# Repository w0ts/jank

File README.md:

# Jank

> ## [→ w0ts.github.io/jank](https://w0ts.github.io/jank/)
> **What Jank is, how to install it from the browser, and the device's control page: on the site.**
> This README is for developers.

Jank brings computers, MIDI gear and modular gear into one Ableton Link session with no router: the group mode of
[Optimist](https://github.com/w0ts/optimist), the open firmware for the FM-1 synth. Link is Ableton's trademark; Jank is
not an Ableton product.

## Build and flash

```
scripts/install_idf.sh       # once: ESP-IDF v5.5.6 into the scratch folder (needs Python 3.13)
make build                   # scripts/build.sh auto: the release image, XIAO or jank mini 3, told apart at the start
make flash                   # build, then install on the running device: the JANK drive, else USB MIDI (scripts/ota.py)
bash tests/run.sh            # the host tests (C and the pages' JS)
```

Build files stay in `$JANK_SCRATCH` (default `worktrees/jank-scratch/`, git-ignored). Boards, builds, partitions and
updates: [docs/firmware.md](docs/firmware.md), [docs/boards.md](docs/boards.md), [docs/usb.md](docs/usb.md).

## Site and releases

- `make page` expands `page/src/*.html` (+ `ui/`) into `page/`. The site is built from `main` by the Pages workflow
  (`.github/workflows/pages.yml`, the shared w0ts site builder with `site.json`) whenever `page/` changes; `make publish-page` runs it by hand.
  No branch holds the site.
- A `v*` tag runs `.github/workflows/release.yml`: it builds the release image, `scripts/publish_firmware.py` writes its
  assets (every flash part and the manifest `jank-auto-TAG.json`), the release carries them, and the Pages workflow lays
  them out under the site's `firmware/` (with `firmware/index.json`) for the Install page's browser flasher.

## Hardware

- [jank mini 3](hardware/jank-mini-3/README.md): our board around the Waveshare ESP32-S3-LCD-2, and its printed case
  (`hardware/jank-mini-3/case/`). The bare device is a Seeed XIAO ESP32-S3 alone.

## Docs

[On the air](docs/air.md) · [USB](docs/usb.md) · [MIDI clock](docs/midi.md) · [boards and pins](docs/boards.md) ·
[LCD-2](docs/lcd2.md) · [LINE IN](docs/linein.md) · [beat follow](docs/beat.md)

**Beat follow's network weights are not in the firmware or in this repository.** The firmware reads them from its
`beatw` partition; the Install page adds madmom's model (CC BY-NC-SA 4.0, non-commercial) at the user's click, from
madmom's own repository, in the user's browser ([docs/beat.md](docs/beat.md)).

## Licensing

The firmware (`firmware/`, `core/`, `tests/`, `scripts/`) is GPL-3.0-only, as it links Optimist's `link.c`
(`third_party/link`, copied from fm1-base, see its README). The control page and its test are MIT. The hardware
scripts carry GPL-3.0-only SPDX tags (`hardware/pcb/lib/stitch.py` CC0-1.0); the KiCad footprint of the XIAO is Seeed's,
CC BY-SA 4.0. See [LICENSE](LICENSE).

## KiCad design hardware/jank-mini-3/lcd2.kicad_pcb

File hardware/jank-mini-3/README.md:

# jank-mini-3: the LCD-2 module board (FINAL 2026-11-19: review rounds 9 and 10 clean; not ordered)

A removable add-on board for a Waveshare ESP32-S3-LCD-2 (sku 30306). The LCD-2 sits in our notch, its PCB level with
ours; two bridge strips (strip/), each with two 1 x 14 sockets, plug onto its pins and onto our J15 / J16 (standard
male headers): nothing is soldered between them, a printed support in the case holds the strips from below. No screws.
The plan, cost, sketches and bench tests are in `worktrees/lcd2-addon-scratch/` (README.md there). **The current
order remarks and bench steps are in "Ordering" near the end; the review-round sections are history.**

| file | what |
|---|---|
| `parts.py` | the one parts table: every part, value, LCSC code, pad -> net, the GPIO map, the LCD-2's rows |
| `make_schematic.py` | writes `lcd2.kicad_sch`, `lib/chip.kicad_sym`, `fab/intended-nets.json` (mini 2.2's generator) |
| `check_nets.py` | the KiCad netlist against parts.py, plus the pin rules (LCD-2 rows, ADC1, glitch / pull rules, pull-downs, boost < clamp) |
| `sim/` | `power.py`, `clamp.py`, `host.py`, `midi_cv.py`, `linein_esd.py` and their `.txt` results |
| `lcd2-schematic.pdf` | the sheet (one label per pin: it reads as a netlist) |

Rebuild and check (KiCad 10, ngspice 47, Python with numpy):

```bash
cd hardware/jank-mini-3 && python3 make_schematic.py && kicad-cli sch erc --severity-all -o fab/erc.rpt lcd2.kicad_sch && kicad-cli sch export netlist --format kicadxml -o fab/lcd2.net.xml lcd2.kicad_sch && python3 check_nets.py fab/lcd2.net.xml fab/intended-nets.json
```

```bash
cd hardware/jank-mini-3/sim && for s in power clamp host midi_cv linein_esd; do python3 $s.py > /dev/null || echo FAIL $s; done
```

USB (mots, 2026-11-17): the LCD-2's own USB-C sits at the case's side wall and is used directly for a computer or a
charger. For host mode a standard short cable outside the box joins it to J1 (TO ESP, USB-C, VBUS and CC open); D+ / D-
run straight to J4 (TO DEVICE, USB-C), whose VBUS carries only the host signal (R93 / D16 from U21).

OUT gives hosted gear only a 680 ohm host signal on VBUS, never power (mots, 2026-11-17: the small cell is not drained). Bus-powered gear needs its own power or a powered hub.

## jank-mini-3 layout (mots, 2026-11-18)

Board 95.5 x 82 mm (93 x 74 until round 3: +2.5 mm wide for the mid-mount USB-C pair, +4 mm above and below the
LCD-2 for the bands beside it, mots 2026-11-18), the LCD-2 in a notch open to the left edge (its PCB level with ours,
LCD-2 centred). Two bridge strips (strip/, 37.06 x 10 mm: two 1 x 14 sockets C2905420 3.81 mm apart, pin k straight
across to pin k) join its pins to ours under the board; our J15 / J16 are standard male headers (C2905490: 2.5 mm
plastic, 6 mm pin), the same stack as the LCD-2's own header, so both seat ~6 mm into the 8.5 mm sockets and the strip
hangs ~11 mm below. **Assembly (mots):** solder J15 / J16 into our board from below with a strip and the LCD-2 plugged
on as a jig (their 1.2 mm holes let a loose header sit ~0.3 mm off its row); then the strips plug on and off.
**The cell (mots, 2026-11-19, after review 6A R1): on the LCD-2's own MX1.25 connector, not on this board.** One EEMB
LP103454 2000 mAh 1S LiPo (34.5 x 56 x 10.6 mm, its own PCM, a JST PHR-02 plug) through an adapter lead mots makes: a
PH2.0 pigtail that mates with the cell's plug, soldered to an MX1.25 (Molex PicoBlade 51021 type) 2-pin pigtail, red to
red, heat-shrunk; MX1.25 pigtail colours vary: meter which pin is + and check it lands on the LCD-2's pin 1 (VBAT) before
the first plug-in. The LCD-2 charges it (ETA6098, ~2 A, about 1 C) on its own copper, and gives VBAT on P2.14, which our
5 V boost uses on battery (~0.2 A, VBAT 0.3 mm here). The cell lies on the case floor under the right part (x ~50-84.5),
its lead end toward +y or -y; the lead runs to the LCD-2. (J18, a PH2.0 socket on our VBAT, was tried and left again:
it put the whole charge through the LCD-2's unmeasured trace to P2.14.) **The cell must have its own PCM:** nothing on
the LCD-2 or on ours protects it. Under the board, hand-soldered by mots (fab/lcd2-hand.csv): the DINs, the jacks,
J15 / J16, and on top the two USB-C J1 / J4 (through hole, soldered from below). On top, by JLC: every SMD part.
Walls: USB-C TO ESP (J1) + TO DEVICE (J4) side by side (13 mm), right of the two TRS jacks, on the top wall: GCT
USB4085-GF-A (C7095263), on top at the edge, 3.46 mm tall (see "Through-hole USB-C" below), MIDI (2 TRS + 2 DIN) top, CLOCK / RESET right, LINE IN bottom under its LCD-2 pins; the LCD-2's own USB-C on the left
wall. One 24 mm cross D-pad: no part under it.
The GPIO map is assigned from the layout (tools/gpio_opt.py, the joint search tools/layout_opt.sh) within
check_nets' pin rules.

```bash
cd hardware/jank-mini-3 && sh tools/route_try.sh 82 1      # place + route one attempt into .t/route-h82/ (never touches lcd2.kicad_pcb)
```

### Review round 1 (2026-11-18: worktrees/mini3-review-A, -B) and what changed

- Fixed: the cells' 2 A path at signal width (BNEG / FET_D 1.0 mm, CELL nets 0.8 mm, routed first, 0.6 mm drill
  power vias, the DW01A's ground pins and C106 a thin tap; check_board item 7 checks widths); LINE IN plug detect
  (LIN_DET on IO18, BTN_DOWN on IO21; the WEAK rule in check_nets / gpio_opt); a 3 A fuse per cell (F1 / F2) and
  R164 470 ohm (reversed cell); the boost's output caps beside U18's VOUT / GND pins (U18 turned, L5 under SW); the
  cut-out as a notch (no 0.2 mm sliver); thermal reliefs on through-hole pads; USB-C 13 mm apart; silk text >= 1 mm.
- Open, mots: the strip's soldered side and J15 / J16's header (soldering to our board needs ~12 mm of pin below the
  plastic, not on LCSC); the cells' charge rate (the LCD-2 charges at 2 A, about 2 C for 450 / 550 mAh cells: check
  the cells' datasheet; R15 on the LCD-2 sets it, bench test 2 measures it); meter the DIN-504B-M10 and PJ-320A pad
  numbering before ordering; meter every cell lead before plugging it in (red = the "+" pin 1).
- Not done: the case for this layout, the strip's fab files.

### Review round 2 (2026-11-18: worktrees/mini3-review2-A, -B) and what changed

- Fixed: CLOCK / RESET on the PJ-320A's D (tip) and A (sleeve) again (KiCad's PJ320D footprints name them; review 2A);
  the boost's output loop (no bottom track under U18 / C100 / C101, 2 GND vias at each ground pad); 3 GND vias at
  U23's source pin (the cells' return); C106 beside U22; thermal spokes 0.4 mm; the Gerbers, drill and CPL share the
  board's lower-left origin (make_assembly refuses a board without it; review 2B R2); the USB-C mid-mount, board
  +2.5 mm (mots; review 2B R3); check_board item 3 checks the notch, item 7 is a resistor network (a thin loop that
  carries little current passes, one that carries more per mm than the minimum track fails).
- Ground loops: as mini 2.2 (its README, "Ground loops"): MIDI OUT isolated at the receiver's opto, the shield / sleeve
  grounded here only; CLOCK / RESET sleeves through 100 ohm (R120 / R121), LINE IN's through 100 ohm (R39) with the
  sleeve-sensing input; USB TO ESP / TO DEVICE on GND directly (no isolator). Hum-free: the cell with Wi-Fi / Link, no USB to an
  earthed computer while CLOCK / RESET or LINE IN go to earthed gear.

### Review round 3 (2026-11-18: worktrees/mini3-review3-A, -B) and what changed

- Placement for routing (mots): the USB-C pair right of the TRS jacks, the TRS drivers by their jacks, the protector
  pair side by side, the 5 V aux group split, the board 82 mm; U5 turned (its data pins face the USB-C); the pin map
  re-assigned by tools/gpio_opt.py for length, crossings and straightness. Routed clean (route.py: +3V3 at signal
  width, a repair round on whole nets with every track locked; tools/bridge_islands.py, stitch_island.py, widen_hot.py).
- Fixed after the review: the USB-C notch to the maker's drawing (6.75 deep, dog-bone reliefs, slots 0.6 x 1.4 / 1.8,
  signal pads trimmed to 0.2 mm from the edge: lcd2.kicad_dru, paste on the 4 shell legs: pin-in-paste); D3 / D17
  SS34F in SMAF (1.06 mm, was SMA up to 2.4 mm against the lid's 2.1 mm); the boost's feedback divider R134 / R135 at
  U18's FB pin, no bottom track under L5; top labels off the D-pad cap and off part bodies; the bridge strip's fab
  files (strip/fab/strip-gerbers.zip, pin-1 end marked); check_nets' J1 VBUS rule for the new part's pads.
- Firmware (firmware/main): MIDI TX inverted in the UART (BOARD_MIDI_TX_INVERT), MIDI OUT 2 on GPIO 9, the mini 3's pins
  in board.h; HOST_EN (GPIO 17) is defined but nothing drives it on this board yet: host mode stays off.
- mots, before ordering: trim every through-hole lead on the bottom parts to 1 mm or less (the tails come up 1.4 to
  1.9 mm through the top, under a lid 2.1 mm above it); check JLC's placement preview for the rotations of D16 / U19,
  Q1 / Q10-Q13, D7 / D10 / D11 / D14 and the USB-C (EasyEDA footprints, origins not cross-checked). On the order: board
  thickness 1.6 mm (the mid-mount USB-C needs it) and the remark "THT-solder the 8 USB-C shell legs" (the stencil's
  pin-in-paste gives them too little solder; otherwise mots fills the slots from below).
- Decided, mots: the LCD-2 is not modified (R15 stays: 2 A charge); the cell is one 1S LiPo on the LCD-2's own MX1.25 through a
  PH2.0 -> MX1.25 adapter lead (2026-11-19, after review 6A R1); the strips are soldered to our board; Claude designs the case after the reviews (the USB-C
  overmolds need one ~26 x 7 mm opening reaching into the lid).

### Review round 4 (2026-11-19: worktrees/mini3-review4-A, -B) and what changed

- mots: the cells, sockets, fuses, sharing resistors and the DW01A + FS8205A protector left this board (one cell on
  the LCD-2's own connector); VBAT now only feeds our 5 V boost (route.PWR / check_board: 0.3 mm minimum).
- The bridge strip: one socket (the LCD-2) and a row of plated holes (our long pins), review 4B W1: with two sockets the
  LCD-2's pins would have reached 0.6 mm into theirs.
- J4's ESD (U5) and its VBUS parts (C28, D16, Rp R160 / R161) moved right behind J4 (review 4A R6); the boost's whole
  feedback chain (R134 / R135 / R154 / R136) at U18's FB pin (4A R5); R167 4.7k on D3's anode against its leakage on
  battery (4A R7); the VBUS sense divider 10k / 15k, 3.0 V at 5 V (4A R8); no paste on unfitted parts (4B N3); the
  USB-C slots 0.6 x 1.4 / 1.2 (the legs hold the part) and its signal pads from 0.20 mm off the notch (4B R1).
- J4 carries VBUS on one pad pair only (A4 / B9); the other pair is open: a plug ties its four VBUS pins together, both
  orientations reach it (review 4A checked it).
- mots, later the same day: 2000 / 1100 mAh cells come with PH2.0 plugs, the LCD-2 has MX1.25, so ONE PH2.0 socket (J18)
  came back on VBAT / GND (no protector: the cell's own PCM); VBAT back to 0.75 mm (route.PWR 1.0 mm, check_board 7).
- Firmware: the low-cell cutoff (the LCD-2's own battery divider on GPIO5) is for the firmware + webpage session.

### Review round 5 (2026-11-19: worktrees/mini3-review5-A, -B) and what changed

- A W1 (the README's PH2.0 cell on the LCD-2's MX1.25): answered by J18 above. A R1 (2 A): mots, 2026-11-19: the LCD-2
  stays as is; a computer's USB port gives far less, a 2-3 A charger the full 2 A (J18, PH2.0, is rated 2 A).
- B R1: the USB-C signal pads start 0.075 mm from the notch floor (lcd2.kicad_dru 0.07; leads on 0.42 mm of pad, was
  0.30): JLC may ask about copper near the edge, answer "as designed, mid-mount USB-C". B R3: a fourth M2 hole in the
  right part (W - 4, H / 2), between CLOCK and RESET. B R4: the strip's holes 1.15 mm, pads 1.9 mm; its "1" / "14" 1.0 mm.
- Silk: the pin-1 arrows point at pin 1 on either side; D3 / D17's lines 0.15 mm; the date. fab/lcd2-hand.csv lists the
  strip set. The DIN symbol's pin names (pad 4 = DIN 4, pad 2 = DIN 5; the copper was right), the PDF's stale notes
  (V5A 5.00 V, clamp 5.83 V), sim/power.py + host.py with R88 / R89 10k / 15k, C29 and R167 (results: unplug VBUS_B
  0.148 -> 0.071 V, the LCD-2's VCC dip 1.7 -> 0.6 ms; host unchanged).
- mots, before ordering: 1 oz copper (16 tracks at 0.10 mm); JLC's high-precision outline (0.2 mm behind the USB-C's
  body, B R2; for an order JLC assembles only that helps, a dry fit is for hand assembly, 7B N3); on arrival, D+ / D- / CC continuity on J1 / J4.
- mots, before soldering the strips (A R3; round 6A N1: Waveshare's pinout graphic confirms J15 = P1, J16 = P2, pin 14
  at the USB end): on the bare LCD-2 with USB in, the pin at our J15.14 spot reads 5 V and J16.1 3.3 V (the strip's silk
  "1" is a label only). The cell's polarity (A R2, 6A N2): the adapter on the cell, meter its MX1.25 pins: + goes to the LCD-2's pin 1 (VBAT).
  Scope GPIO9 and GPIO13 at boot (A: MIDI OUT 2's pin; 6A N8: the S3 drives it low for an instant, harmless).
- The case (Claude, after the reviews): NOT a post under the D-pad centre (B R3 proposed (64.75, 41)): the cell lies
  there (EEMB LP103454, 34.5 x 56 x 10.6 mm, x ~50-84.5 on the floor). The new M2 hole at (91.5, 41) is clear of it;
  with H4 the D-pad sits inside the holes' support (6B N6: ~0.4 mm, ~550 microstrain at 10 N); a case rib under the D-pad
  can still back it, the cell's lead end toward +y (the DIN bodies reach the floor down to y 16.3, 7B N6).

### Review round 6 (2026-11-19: worktrees/mini3-review6-A, -B) and what changed

- 6B R1: J18's "+" lay under its own housing: now a "+" on top beside pad 1 (where mots solders) and one on the bottom
  behind the housing; J18's silk lines 0.15 mm. Stale texts (6A N9): the PDF's VBAT note, parts.py's old cell comment,
  midi.c's comment on the S3's pin routing (6A N8), check_board's VBAT width print.
- 6A R1, mots: J18 LEFT the board (VBAT back to 0.3 mm); the cell on the LCD-2's own MX1.25 through an adapter lead.
  The review's text, for the record: 6A R1 (the LCD-2's side): the 2 A charge now runs through the LCD-2's own copper to P2.14 (width unknown) and its
  charge inductor L3 is rated 1.9 A. Ours: J16.14 -> J18.1 42.8 mohm, 1.0 mm, ~7 C at 2 A. Bench test 2 with the cell on
  J18: the real charge current, the drop from the LCD-2's empty battery pad to J18.1, temperatures at P2.14 / L3 / J18 /
  the cell after 20 min with the lid on; above ~60 C on a part or 45 C on the cell, charge only from 1 A sources.
- mots, handling (6A N3-N4): the LCD-2's pins are live whenever its cell is plugged in (J16.13 GND is 0.74 mm from J16.14):
  unplug the cell before seating or removing the LCD-2 and before soldering J15 / J16 or the strips. Plugging the cell in
  makes a short inrush (7A N1, re-simulated with the cell on the MX1.25: 13-30 A for 30-50 us, mostly the LCD-2's own
  capacitors; ours add 1-3 %): plug it 3 times on the bench and check it boots
  each time (a touchy PCM may latch off; USB in releases it). Nothing on our board limits a VBAT short or charges by
  temperature (6A N5, N10: the cell's own PCM only; no NTC on the LCD-2's charger).
- mots, the cell (6B N3, N5): EEMB's drawing shows the leads leaving one 34.5 mm end, about 60 mm long (scaled, not
  measured); on the floor that end faces +y or -y; with the adapter lead (10 cm pigtails) it reaches the LCD-2's MX1.25 under the
  LCD-2. PH2.0 is 2 A with AWG 24: check the leads and the pigtails.
- mots, the order (6B N1, N4): remark "do not pull back J1 / J4 pad copper near the notch: mid-mount USB-C, as designed";
  measure one DIN-504B-M10's depth below the board (LCSC 19.6 mm, a HOOYA drawing 20.9 mm) before the case.
- Firmware (for the firmware + webpage session, 6A N7): the LCD-2's battery reading on IO5 sits at its end of that path:
  ~40-80 mV low on battery through the MX1.25, the adapter and the cell's PCM (7A N1, estimated 0.1-0.2 ohm; safe for a
  cutoff), ~0.2-0.4 V high while charging at 2 A (do not judge "full" from it on USB). The cutoff drives GPIO4 (V5_EN) low
  and holds it through deep sleep, else R131 keeps the boost on: ~0.2-0.25 mA from the cell (7A N4).

### Review round 7 (2026-11-19: worktrees/mini3-review7-A, -B) and what changed

- 7A: 0 will-not-work, 0 risky. 7B: one risky, the cell's charge through the LCD-2's own MX1.25 (PicoBlade-type contacts
  are usually ~1 A, the charge ~2 A). mots, 2026-11-19: a cell on the LCD-2's own socket is Waveshare's stock design, not
  this board's; kept as a bench note: bench test 2 logs the real charge current and, after 20 min on a 2 A charger with
  the lid on, the temperatures of the MX1.25 housing, the adapter's splice, the LCD-2's L3 and the cell (above ~60 C on a
  part or 45 C on the cell: charge from 1 A sources). The adapter's pigtails 26 AWG or thicker (7A N2).
- The cell's polarity (7A N3): find the LCD-2's MX1.25 "+" contact by a continuity beep to P2.14, unpowered; the adapter's
  + goes there. A reversed cell is survivable for our board, not for the LCD-2.
- Silk: labels avoid signal vias (the CLK_M via printed through "UP", 7B N5); "TO ESP" / "TO DEVICE" below the drawn
  data pair. J18's leftovers (silk branch, parts row, comments) removed (7A N6, 7B N4).
- mots, on arrival: look at the first DIN-504B-M10's underside; V5M runs on the bottom under J5 and V5A / V5M under
  J13 / J14 behind solder mask only; a metal shield there wants Kapton (7A N7). Keep metal off the case floor under the
  board: VBAT runs 55 mm on the bottom over the cell area (7B N9). The tab between J1 and J4 is 0.67 mm of board at the
  edge: the case opening takes the plugs' side loads (7B N7). The maker's drawing says "THICKNESS 0.80MM": order 1.6 mm
  as designed (7B N8). The front shell slots are 1.40 mm for 1.20 mm legs (deliberate since 4B; the maker shows 1.80).

### Review round 8 (2026-11-19: worktrees/mini3-review8-A, -B): clean, the board is FINAL

- 8A and 8B: 0 will-not-work, 0 risky. With round 7 (clean under mots's ruling that the cell on the LCD-2's own MX1.25
  is Waveshare's stock design), two successive clean rounds: mots's rule for final is met. The board was not changed
  after round 8; only these notes and docs/lcd2.md's GPIO43 line.
- mots, the order remarks: "mill the USB-C notch reliefs with a cutter of 1.0 mm or less" (8B N2: 0.9 mm T-bones; a
  cutter of 1.6 mm or more would leave FR4 under the body's corner); "do not pull back J1 / J4 pad copper near the
  notch"; high-precision outline; 1.6 mm; 1 oz; THT-solder the 8 USB-C shell legs.
- mots, before ordering: U19 CJ431 (C3113) pin order 1 REF / 2 K / 3 A, as JSCJ's CJ431D / E and CJ432 sheets give it
  (8A N3; the C3113 sheet itself not read): check it on LCSC's pin picture; the first power-up from a current-limited
  supply (a swapped part would short V5A through R145).
- If the board is ever touched again (8A N1, N2; not needed to work): a 10 uF at L5.1 with its own GND via (the boost's
  input ripple runs ~36 mm to C99), a 100 nF at U21's pins 14 / 7 (C105 sits 13 mm away); bench: scope L5.1 and J16.14.
  8B N3: the PJ307C slots are 0.8 x 1.5 mm (JLC wants 2:1), hand-soldered, at worst a little loose.

### Ordering (2026-11-19): one folder per variant, JLC quotes for 5 units

`make_fab.sh` writes `fab/default/` and `fab/full/`; `strip/fab/bare/` and `strip/fab/assembled/` hold the strip's.
Upload a folder's `gerbers.zip`, then its `bom.csv` and `cpl.csv`. Quotes (jlcpcb.com, headless Chrome through
`scripts/jlcone/`, 2026-11-19, before shipping; DHL showed ~$23.5):

| Variant | What JLC does | Price |
|---|---|---|
| Jank mini 3 default, x5 | top SMD (Standard PCBA: the USB-C C2906290 is "Standard only"); mots solders `fab/default/hand.csv` | $120.18 (mid-mount USB-C, before the switch below) |
| Jank mini 3 full, x5 | also the DINs, jacks and J15 / J16 under the board (Standard, both sides) | $177.70 |
| strip bare, x10 | PCB only | ~$6.10 |
| strip assembled, x10 | both sockets fitted (Economic) | $18.46 |

- JLC flags the USB-C as "difficult to process": it reviews it after the order and may charge for an advanced option.
- The full variant's bottom through-hole rotations come from KiCad as they are: check JLC's placement preview.
- The strip (mots's idea, 2026-11-19): two sockets, our J15 / J16 standard male headers (C2905490), the case holds
  the strip from below; 10 mm wide (JLC assembles nothing under 10 x 10 mm). Not covered by review rounds 7 / 8.
- The BOM has one line per LCSC code (JLC refuses two lines matched to one part).

### Through-hole USB-C (mots, 2026-11-19): GCT USB4085-GF-A instead of the mid-mount C2906290

- Why: the mid-mount part is "Standard only" at JLC (5 boards $120.18) and its 0.5 mm SMD pads need hot air. The GCT
  USB4085-GF-A (C7095263, $1.40) is through hole (0.85 mm pitch, two rows 1.35 mm apart), soldered by hand with an
  iron from below; the rest goes Economic: **5 boards $50.89** (quoted 2026-11-19), J1 / J4 on `fab/default/hand.csv`.
- Footprint: JLC's (EasyEDA) origin, pads per GCT's drawing USB4085 rev B sheet 2 (16 x 0.40 mm holes, 0.65 mm pads,
  shell slots 0.60 x 2.10 / 1.40); 3D model KiCad's. On top at the top edge, mouths 0.3 mm past it, no notches; the
  part stands 3.46 mm above the board (the mid-mount 1.56 mm): the case's USB openings move up.
- `lcd2.kicad_dru`: GCT's layout leaves 0.45 mm between neighbouring holes (JLC's general rule 0.5 mm, different nets);
  JLC stocks and wave-solders this part; the rule allows 0.44 mm between J1's / J4's own holes only.
- Re-routed only the USB corner (`.t/swap_usb_th.py`, then the repair pass with the rest locked). CC2 is in the front
  row; R160 now serves CC2O and R161 CC1O (both 56k Rp to HOST5), so the CC paths from U5 no longer cross.
- `make_board.USB_MID = True` brings the mid-mount layout back (notches, usb_fan / usb_pair).

### Review round 9 (2026-11-19: worktrees/mini3-review9-A, -B): clean (0 will-not-work, 0 risky)

- Notes folded in: this README's stale mid-mount and old-strip text replaced; the order remarks and bench steps below are
  the current ones (the earlier rounds' remarks about notches, reliefs and shell legs are void). The repair pass also
  moved 3 GND stitching vias by the boost (9B N5): GND only, DRC clean. JLC wave-soldering this exact layout is not
  verified (9B): the order remark below asks them to keep it.
- For the firmware session (9A N3): host mode should set `BOARD_VBUS_SENSE_GPIO 10` for lcd2, raise HOST_EN only while
  VBUS_SENSE reads low and drop it if it rises (a swapped cable puts J4's host signal on the LCD-2's 5 V, harmless).
- If the board is touched again: a GND via by U5's GND pad (9A N1: its top-pour island reaches GND 4.9 mm away); the
  USB4085's 0.06 mm silk dot (9B N8).

## Ordering (current, 2026-11-19)

What to order for 5 units (option 2, mots, 2026-11-19): JLC: Jank mini 3 x5 from `fab/default/` (Economic, top
side), the strips x10 bare from `strip/fab/bare/` (1.6 mm); LCSC: the parts in `fab/default/hand.csv` plus 2 strip
sockets C2905420 per strip (spares: +2 USB4085, +4 sockets, +2 of each jack, DIN and header). Assembled strips instead:
`strip/fab/assembled/` (Economic, 10 mm wide for JLC's 10 x 10 mm minimum).

Order remarks for JLC (Jank mini 3):
- 1.6 mm, 1 oz copper (tracks down to 0.10 mm), lead-free HASL; "Confirm Production file: Yes" (10B N2: shows what
  JLC's CAM did to J1 / J4's rings and where its tooling holes go).
- "J1 / J4 GCT USB4085: 0.40 mm holes in 0.65 mm pads and 0.44-0.45 mm hole spacing as in the maker's recommended
  layout; please do not enlarge the pads or reduce the holes; breakout acceptable" (9B N1: JLC's ring minimum is 0.18 mm).
- Default variant (`fab/default/`, Economic): JLC fits the top SMD parts only. Full (`fab/full/`, Standard both sides):
  check J1 / J4's position and rotation and every bottom part's rotation in JLC's placement preview before paying.

mots's fallback (2026-11-19): if J1 / J4 do not work, USB host mode is regained with a powered USB hub on the LCD-2's
own USB-C; the rest of Jank works without them.

Bench steps (mots), in this order:
- Before paying: JLC's placement preview for the polarised top parts (default variant), every part in the full one.
- Before fitting anything else: U19 CJ431 pin order on LCSC's picture (1 REF, 2 K, 3 A); first power-up from a
  current-limited supply.
- While the LCD-2 serves as the jig for soldering J15 / J16: no cell and no USB on it. Trim the bottom tails after.
- The spare 0 ohm lands (10A N3): cut JP8 before bridging R123 (else the 5 V boost meets the LCD-2's 3.3 V rail);
  lift Q10-Q13 and un-invert the TX before bridging R126-R129 (else a GPIO is shorted to GND).
- J1 / J4 from below: their signal tails end flush with the board's bottom (1.60 mm), the front shell legs 0.8 mm short
  of it (fill those slots); fine tip, flux. Then meter: J4 VUSB against GND and CC1O, J1's VBUS pairs against GND,
  neighbouring pins against each other, D+ / D- continuity J1 -> U5 -> J4 (9A N2, 9B N2).
- The LCD-2's rows (J15 = P1, J16 = P2, pin 14 at the USB end) and the strips' seating on the dry fit; measure the
  LCD-2's PCB thickness (its top should sit level with ours).
- The case: the LCD's front stands ~4.1 mm above our top (sets the lid height, 10B N5; scaled from Waveshare's
  drawing), its own USB-C reaches ~0.7 mm past our left edge; J1 / J4 stand 3.46 mm, their mouths at y -0.255; the plugs' overmolds span about -1.4 to +5.1 mm about the
  board's top: the lid needs a raised pocket ~18 x 9.3 mm and wall openings for the overmolds (9B N4); label TO ESP /
  TO DEVICE on the case (the board's "TO DEVICE" is on the bottom silk).

### Review round 10 (2026-11-19: worktrees/mini3-review10-A, -B): clean, the board is FINAL

- 10A and 10B: 0 will-not-work, 0 risky; with round 9, two successive clean rounds (mots's rule). No copper change
  since round 9; notes folded into "Ordering" above.
- For a later board (10A N1, N2): ESD on CLOCK / RESET sleeves (R120 / R121 0402 alone), 0.5 W MIDI TRS resistors
  against a stiff negative output patched in.

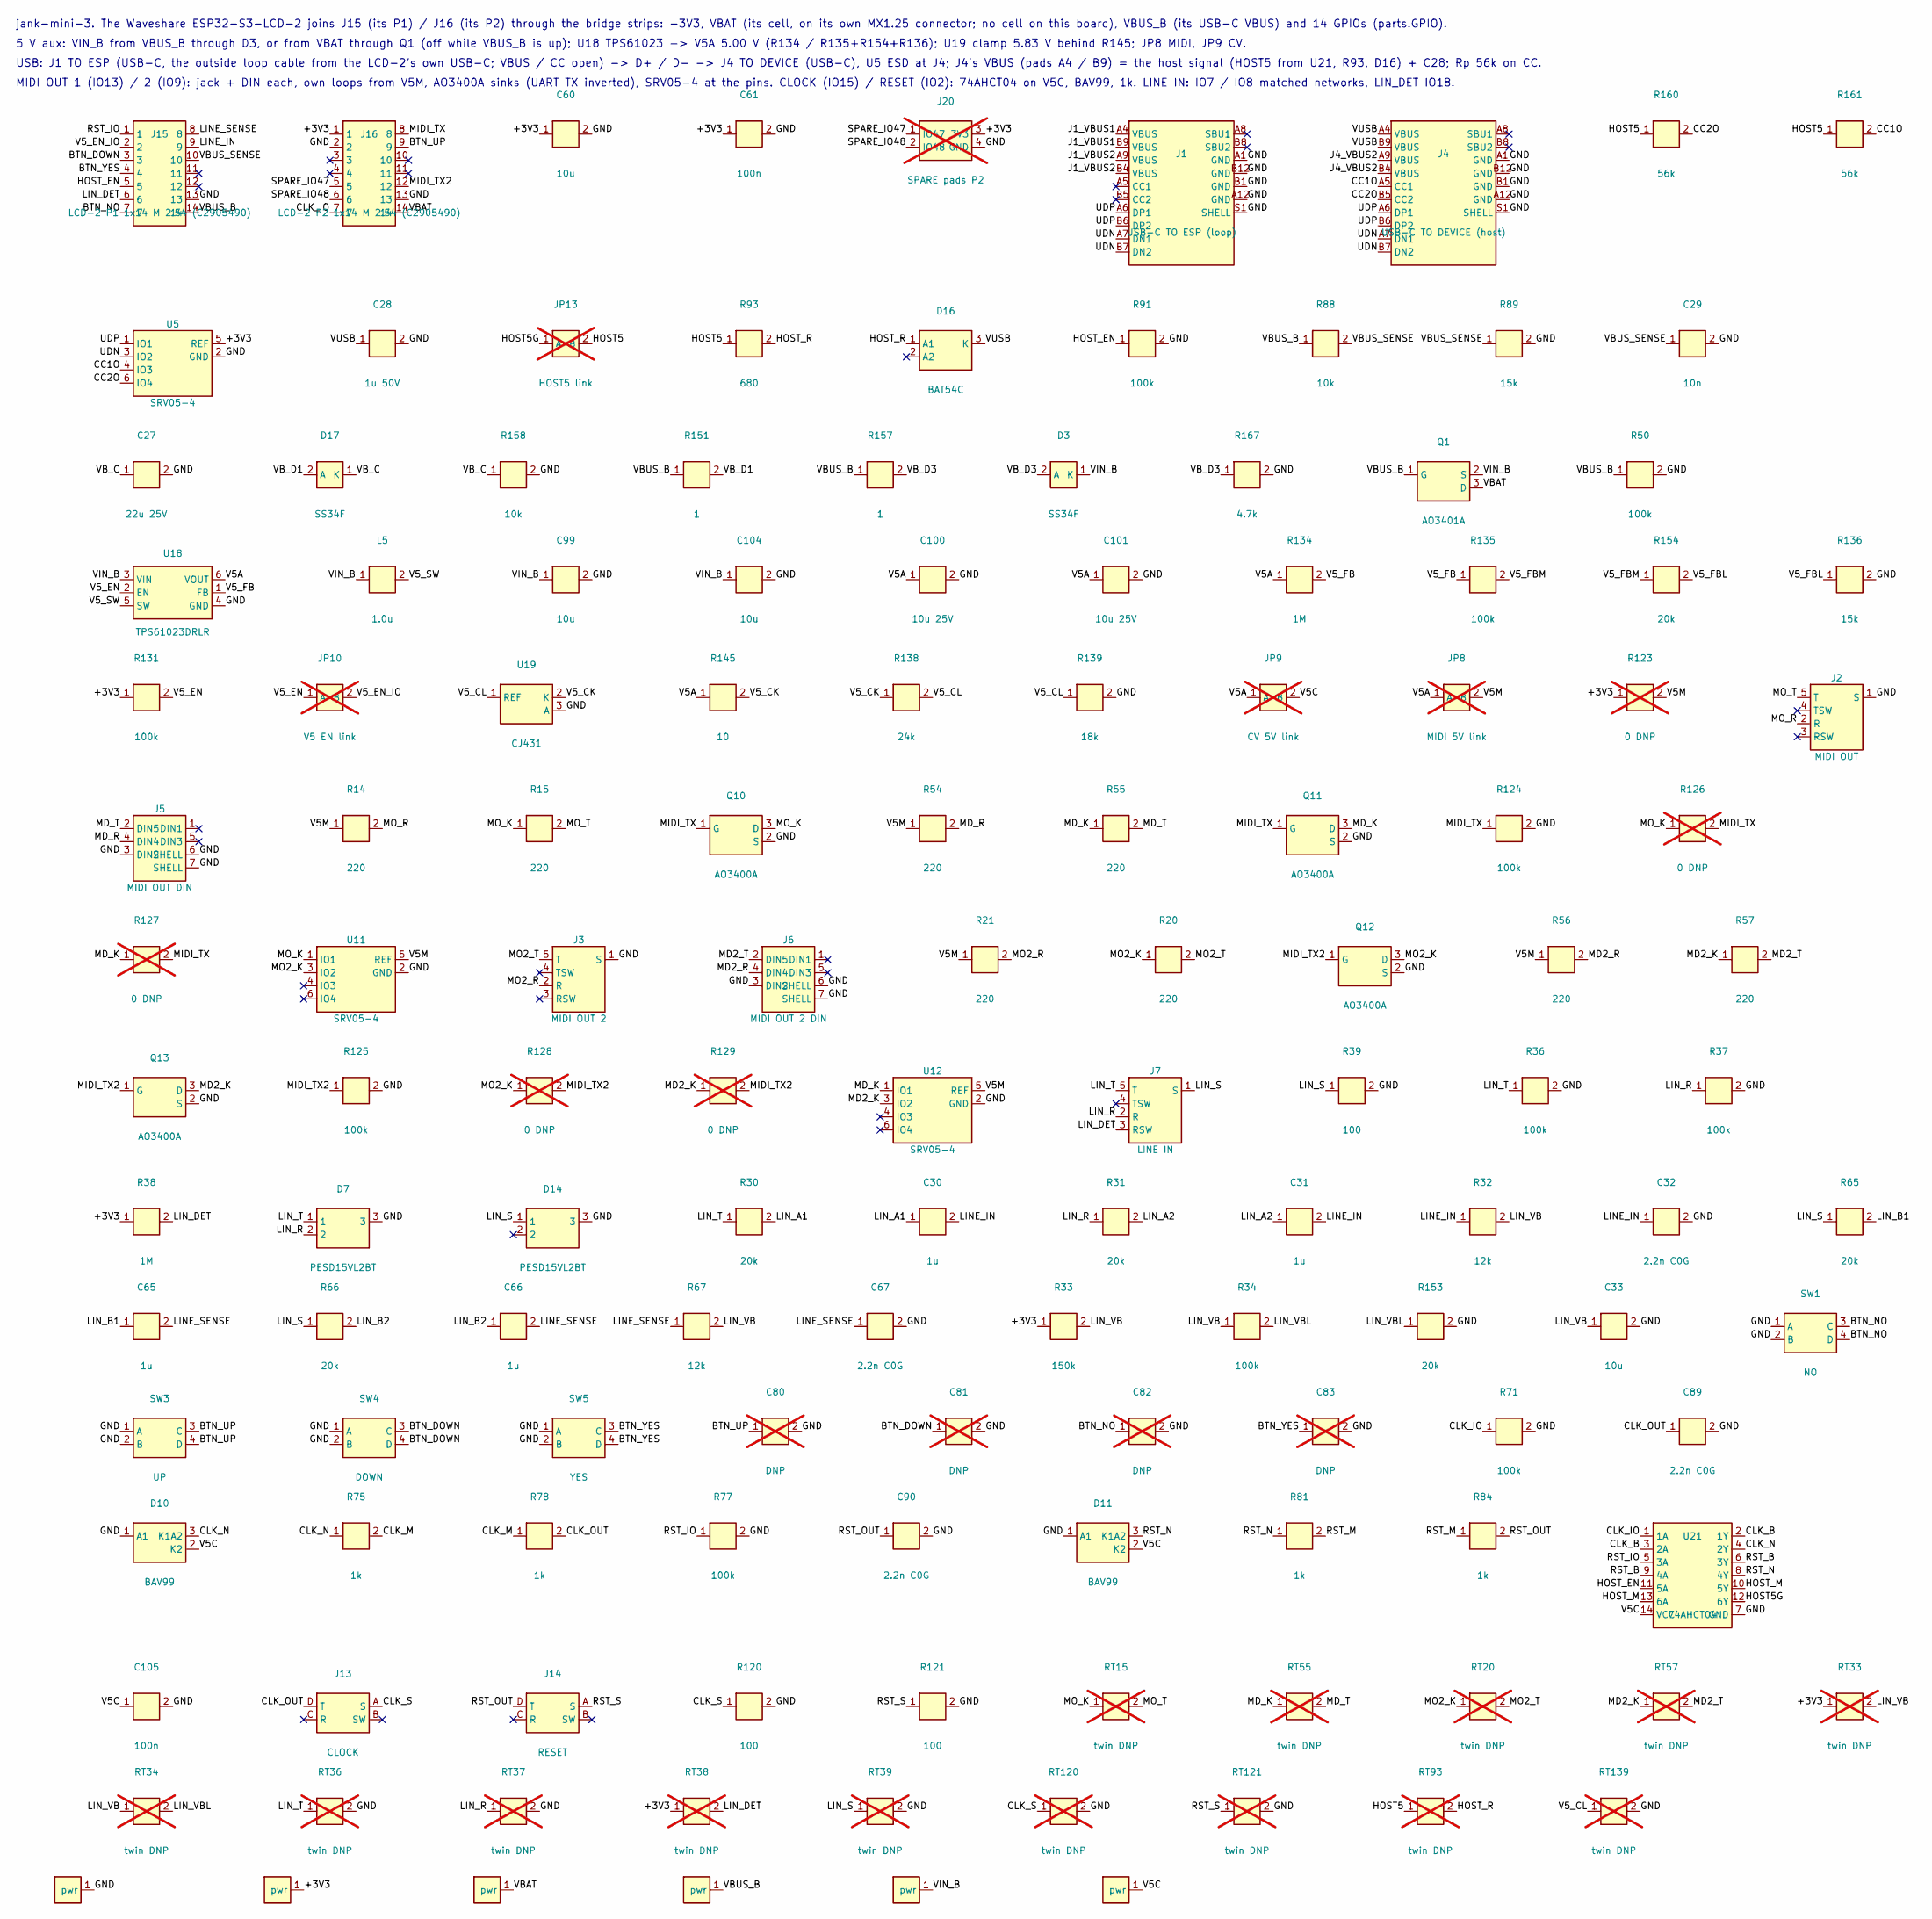
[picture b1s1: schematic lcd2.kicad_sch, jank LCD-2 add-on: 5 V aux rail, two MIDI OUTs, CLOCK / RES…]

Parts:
C27: 22u 25V; C0805; LCSC C45783
C28: 1u 50V; C0603; LCSC C15849
C29: 10n; C0402; LCSC C15195
C30, C31, C65, C66: 1u; C0402; LCSC C52923
C32, C67, C89, C90: 2.2n C0G; C0603; LCSC C2991172
C33, C60, C99, C104: 10u; C0603; LCSC C19702
C61, C105: 100n; C0402; LCSC C1525
C80, C81, C82, C83: DNP; C0603_NP; not fitted
C100, C101: 10u 25V; C0805; LCSC C15850
D3, D17: SS34F; SMAF_L3.5-W2.6-LS4.7-RD-1; LCSC C18199199
D7, D14: PESD15VL2BT; SOT-23_L2.9-W1.3-P1.90-LS2.4-BR; LCSC C38838
D10, D11: BAV99; SOT-23_L2.9-W1.3-P1.90-LS2.4-BR; LCSC C2500
D16: BAT54C; SOT-23-3_L2.9-W1.6-P1.90-LS2.8-BR; LCSC C37704
J1: USB-C TO ESP (loop); USB-C-TH_GCT_USB4085-GF-A; LCSC C7095263
J2: MIDI OUT; AUDIO-TH_PJ307C; LCSC C16684
J3: MIDI OUT 2; AUDIO-TH_PJ307C; LCSC C16684
J4: USB-C TO DEVICE (host); USB-C-TH_GCT_USB4085-GF-A; LCSC C7095263
J5: MIDI OUT DIN; CONN-TH_DIN-504B-M10; LCSC C2939346
J6: MIDI OUT 2 DIN; CONN-TH_DIN-504B-M10; LCSC C2939346
J7: LINE IN; AUDIO-TH_PJ307C; LCSC C16684
J13: CLOCK; AUDIO-TH_PJ-320A-4P-DIP; LCSC C18185602
J14: RESET; AUDIO-TH_PJ-320A-4P-DIP; LCSC C18185602
J15: LCD-2 P1 1x14 M 2.54 (C2905490); HDR-TH_14P-P2.54-V-F; LCSC C2905490
J16: LCD-2 P2 1x14 M 2.54 (C2905490); HDR-TH_14P-P2.54-V-F; LCSC C2905490
J20: SPARE pads P2; PADS4_SMD; not fitted
JP8: MIDI 5V link; SJ2C_SMD; not fitted
JP9: CV 5V link; SJ2C_SMD; not fitted
JP10: V5 EN link; SJ2C_SMD; not fitted
JP13: HOST5 link; SJ2C_SMD; not fitted
L5: 1.0u; IND-SMD_L2.0-W1.6-1; LCSC C337892
Q1: AO3401A; SOT-23_L2.9-W1.3-P1.90-LS2.4-BR; LCSC C15127
Q10, Q11, Q12, Q13: AO3400A; SOT-23_L2.9-W1.3-P1.90-LS2.4-BR; LCSC C20917
R14, R15, R20, R21, R54, R55, R56, R57: 220; R1206; LCSC C17957
R30, R31, R65, R66, R153, R154: 20k; R0402; LCSC C25765
R32, R67: 12k; R0402; LCSC C25752
R33: 150k; R0402; LCSC C25755
R34, R36, R37, R50, R71, R77, R91, R124, R125, R131, R135: 100k; R0402; LCSC C25741
R38, R134: 1M; R0402; LCSC C26083
R39, R120, R121: 100; R0402; LCSC C25076
R75, R78, R81, R84: 1k; R1206; LCSC C4410
R88, R158: 10k; R0402; LCSC C25744
R89, R136: 15k; R0402; LCSC C25756
R93: 680; R0402; LCSC C25130
R123, R126, R127, R128, R129: 0 DNP; R0402_NP; not fitted
R138: 24k; R0402; LCSC C25769
R139: 18k; R0402; LCSC C25762
R145: 10; R0402; LCSC C25077
R151, R157: 1; R0805; LCSC C25271
R160, R161: 56k; R0402; LCSC C25796
R167: 4.7k; R0402; LCSC C25900
RT15, RT20, RT33, RT34, RT36, RT37, RT38, RT39, RT55, RT57, RT93, RT120, RT121, RT139: twin DNP; R_TWIN_HAND; not fitted
SW1: NO; SW-SMD_4P-L5.1-W5.1-P3.70-LS6.5-TL_H1.5; LCSC C318884
SW3: UP; SW-SMD_4P-L5.1-W5.1-P3.70-LS6.5-TL_H1.5; LCSC C318884
SW4: DOWN; SW-SMD_4P-L5.1-W5.1-P3.70-LS6.5-TL_H1.5; LCSC C318884
SW5: YES; SW-SMD_4P-L5.1-W5.1-P3.70-LS6.5-TL_H1.5; LCSC C318884
U5, U11, U12: SRV05-4; SOT-23-6_L2.9-W1.6-P0.95-LS2.8-BL-1; LCSC C7420376
U18: TPS61023DRLR; SOT-563_L1.6-W1.2-P0.50-LS1.6-BR; LCSC C919459
U19: CJ431; SOT-23-3_L2.9-W1.6-P1.90-LS2.8-BR; LCSC C3113
U21: 74AHCT04; TSSOP-14_L5.0-W4.4-P0.65-LS6.4-BL; LCSC C8190

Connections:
/+3V3: C60.1, C61.1, J16.1, J20.3 (3V3), R33.1, R38.1, R123.1, R131.1, RT33.1, RT38.1, U5.5 (REF)
/BTN_DOWN: C81.1, J15.3, SW4.3 (C), SW4.4 (D)
/BTN_NO: C82.1, J15.7, SW1.3 (C), SW1.4 (D)
/BTN_UP: C80.1, J16.9, SW3.3 (C), SW3.4 (D)
/BTN_YES: C83.1, J15.4, SW5.3 (C), SW5.4 (D)
/CC1O: J4.A5 (CC1), R161.2, U5.4 (IO3)
/CC2O: J4.B5 (CC2), R160.2, U5.6 (IO4)
/CLK_B: U21.2 (1Y), U21.3 (2A)
/CLK_IO: J16.7, R71.1, U21.1 (1A)
/CLK_M: R75.2, R78.1
/CLK_N: D10.3 (K1A2), R75.1, U21.4 (2Y)
/CLK_OUT: C89.1, J13.D (T), R78.2
/CLK_S: J13.A (S), R120.1, RT120.1
/GND: C27.2, C28.2, C29.2, C32.2, C33.2, C60.2, C61.2, C67.2, C80.2, C81.2, C82.2, C83.2, C89.2, C90.2, C99.2, C100.2, C101.2, C104.2, C105.2, D7.3, D10.1 (A1), D11.1 (A1), D14.3, J1.A1 (GND), J1.A12 (GND), J1.B1 (GND), J1.B12 (GND), J1.S1 (SHELL), J2.1 (S), J3.1 (S), J4.A1 (GND), J4.A12 (GND), J4.B1 (GND), J4.B12 (GND), J4.S1 (SHELL), J5.3 (DIN2), J5.6 (SHELL), J5.7 (SHELL), J6.3 (DIN2), J6.6 (SHELL), J6.7 (SHELL), J15.13, J16.2, J16.13, J20.4 (GND), Q10.2 (S), Q11.2 (S), Q12.2 (S), Q13.2 (S), R36.2, R37.2, R39.2, R50.2, R71.2, R77.2, R89.2, R91.2, R120.2, R121.2, R124.2, R125.2, R136.2, R139.2, R153.2, R158.2, R167.2, RT36.2, RT37.2, RT39.2, RT120.2, RT121.2, RT139.2, SW1.1 (A), SW1.2 (B), SW3.1 (A), SW3.2 (B), SW4.1 (A), SW4.2 (B), SW5.1 (A), SW5.2 (B), U5.2 (GND), U11.2 (GND), U12.2 (GND), U18.4 (GND), U19.3 (A), U21.7 (GND)
/HOST5: JP13.2 (B), R93.1, R160.1, R161.1, RT93.1
/HOST5G: JP13.1 (A), U21.12 (6Y)
/HOST_EN: J15.5, R91.1, U21.11 (5A)
/HOST_M: U21.10 (5Y), U21.13 (6A)
/HOST_R: D16.1 (A1), R93.2, RT93.2
/J1_VBUS1: J1.A4 (VBUS), J1.B9 (VBUS)
/J1_VBUS2: J1.A9 (VBUS), J1.B4 (VBUS)
/J4_VBUS2: J4.A9 (VBUS), J4.B4 (VBUS)
/LINE_IN: C30.2, C31.2, C32.1, J15.9, R32.1
/LINE_SENSE: C65.2, C66.2, C67.1, J15.8, R67.1
/LIN_A1: C30.1, R30.2
/LIN_A2: C31.1, R31.2
/LIN_B1: C65.1, R65.2
/LIN_B2: C66.1, R66.2
/LIN_DET: J7.3 (RSW), J15.6, R38.2, RT38.2
/LIN_R: D7.2, J7.2 (R), R31.1, R37.1, RT37.1
/LIN_S: D14.1, J7.1 (S), R39.1, R65.1, R66.1, RT39.1
/LIN_T: D7.1, J7.5 (T), R30.1, R36.1, RT36.1
/LIN_VB: C33.1, R32.2, R33.2, R34.1, R67.2, RT33.2, RT34.1
/LIN_VBL: R34.2, R153.1, RT34.2
/MD2_K: Q13.3 (D), R57.1, R129.1, RT57.1, U12.3 (IO2)
/MD2_R: J6.4 (DIN4), R56.2
/MD2_T: J6.2 (DIN5), R57.2, RT57.2
/MD_K: Q11.3 (D), R55.1, R127.1, RT55.1, U12.1 (IO1)
/MD_R: J5.4 (DIN4), R54.2
/MD_T: J5.2 (DIN5), R55.2, RT55.2
/MIDI_TX: J16.8, Q10.1 (G), Q11.1 (G), R124.1, R126.2, R127.2
/MIDI_TX2: J16.12, Q12.1 (G), Q13.1 (G), R125.1, R128.2, R129.2
/MO2_K: Q12.3 (D), R20.1, R128.1, RT20.1, U11.3 (IO2)
/MO2_R: J3.2 (R), R21.2
/MO2_T: J3.5 (T), R20.2, RT20.2
/MO_K: Q10.3 (D), R15.1, R126.1, RT15.1, U11.1 (IO1)
/MO_R: J2.2 (R), R14.2
/MO_T: J2.5 (T), R15.2, RT15.2
/RST_B: U21.6 (3Y), U21.9 (4A)
/RST_IO: J15.1, R77.1, U21.5 (3A)
/RST_M: R81.2, R84.1
/RST_N: D11.3 (K1A2), R81.1, U21.8 (4Y)
/RST_OUT: C90.1, J14.D (T), R84.2
/RST_S: J14.A (S), R121.1, RT121.1
/SPARE_IO47: J16.5, J20.1 (IO47)
/SPARE_IO48: J16.6, J20.2 (IO48)
/UDN: J1.A7 (DN1), J1.B7 (DN2), J4.A7 (DN1), J4.B7 (DN2), U5.3 (IO2)
/UDP: J1.A6 (DP1), J1.B6 (DP2), J4.A6 (DP1), J4.B6 (DP2), U5.1 (IO1)
/V5A: C100.1, C101.1, JP8.1 (A), JP9.1 (A), R134.1, R145.1, U18.6 (VOUT)
/V5C: C105.1, D10.2 (K2), D11.2 (K2), JP9.2 (B), U21.14 (VCC)
/V5M: JP8.2 (B), R14.1, R21.1, R54.1, R56.1, R123.2, U11.5 (REF), U12.5 (REF)
/V5_CK: R138.1, R145.2, U19.2 (K)
/V5_CL: R138.2, R139.1, RT139.1, U19.1 (REF)
/V5_EN: JP10.1 (A), R131.2, U18.2 (EN)
/V5_EN_IO: J15.2, JP10.2 (B)
/V5_FB: R134.2, R135.1, U18.1 (FB)
/V5_FBL: R136.1, R154.2
/V5_FBM: R135.2, R154.1
/V5_SW: L5.2, U18.5 (SW)
/VBAT: J16.14, Q1.3 (D)
/VBUS_B: J15.14, Q1.1 (G), R50.1, R88.1, R151.1, R157.1
/VBUS_SENSE: C29.1, J15.10, R88.2, R89.1
/VB_C: C27.1, D17.1 (K), R158.1
/VB_D1: D17.2 (A), R151.2
/VB_D3: D3.2 (A), R157.2, R167.1
/VIN_B: C99.1, C104.1, D3.1 (K), L5.1, Q1.2 (S), U18.3 (VIN)
/VUSB: C28.1, D16.3 (K), J4.A4 (VBUS), J4.B9 (VBUS)

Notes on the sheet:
jank-mini-3. The Waveshare ESP32-S3-LCD-2 joins J15 (its P1) / J16 (its P2) through the bridge strips: +3V3, VBAT (its cell, on its own MX1.25 connector; no cell on this board), VBUS_B (its USB-C VBUS) and 14 GPIOs (parts.GPIO).
5 V aux: VIN_B from VBUS_B through D3, or from VBAT through Q1 (off while VBUS_B is up); U18 TPS61023 -> V5A 5.00 V (R134 / R135+R154+R136); U19 clamp 5.83 V behind R145; JP8 MIDI, JP9 CV.
USB: J1 TO ESP (USB-C, the outside loop cable from the LCD-2's own USB-C; VBUS / CC open) -> D+ / D- -> J4 TO DEVICE (USB-C), U5 ESD at J4; J4's VBUS (pads A4 / B9) = the host signal (HOST5 from U21, R93, D16) + C28; Rp 56k on CC.
MIDI OUT 1 (IO13) / 2 (IO9): jack + DIN each, own loops from V5M, AO3400A sinks (UART TX inverted), SRV05-4 at the pins. CLOCK (IO15) / RESET (IO2): 74AHCT04 on V5C, BAV99, 1k. LINE IN: IO7 / IO8 matched networks, LIN_DET IO18.

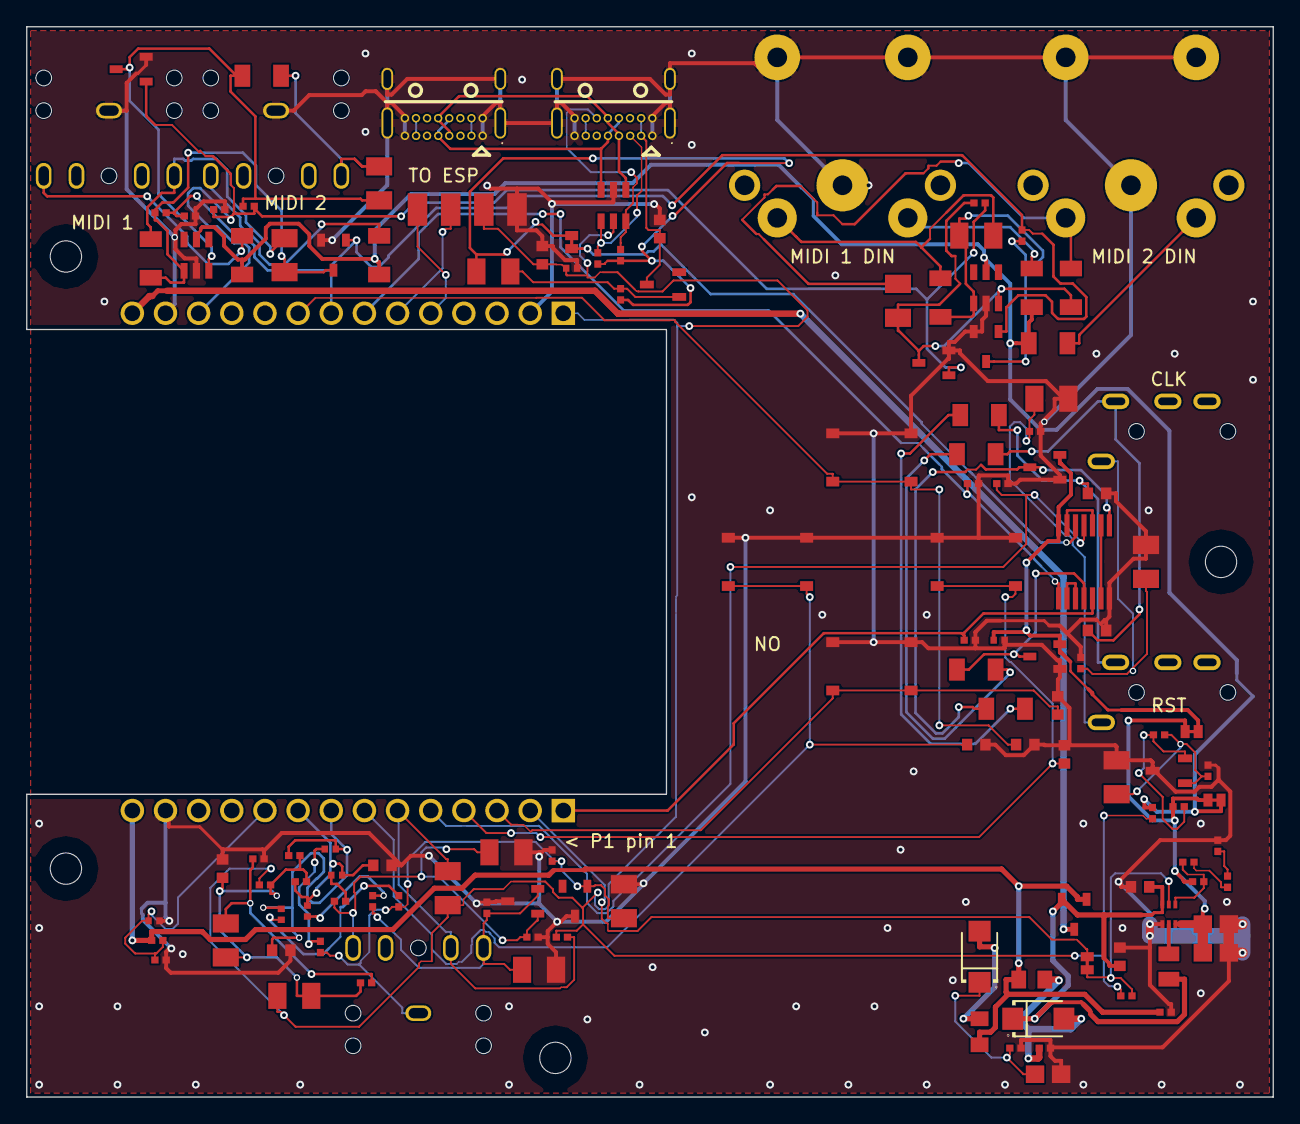
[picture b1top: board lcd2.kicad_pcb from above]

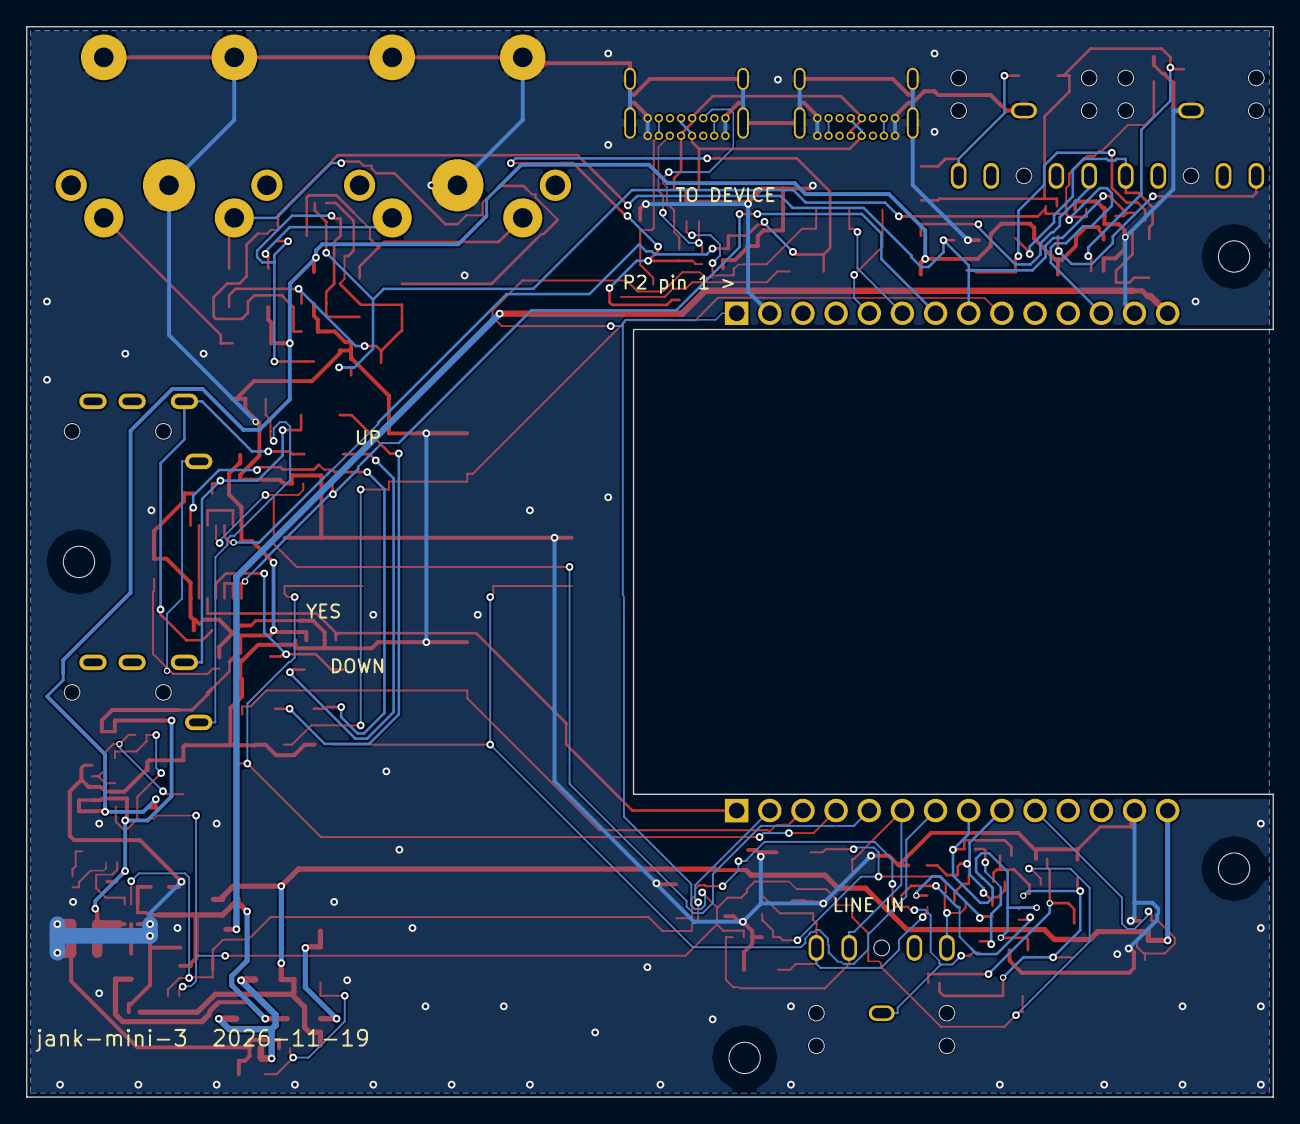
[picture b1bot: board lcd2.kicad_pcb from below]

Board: 2 copper layers, 95.5 x 82.0 mm, 135 parts (9 on the bottom side), 77 nets.

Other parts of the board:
H1, H2, H3, H4: M2; HOLE_M2_2.4

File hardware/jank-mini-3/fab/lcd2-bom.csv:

Comment,Designator,Footprint,LCSC
AO3401A,Q1,SOT-23_L2.9-W1.3-P1.90-LS2.4-BR,C15127
10n,C29,C0402,C15195
100n,"C105,C61",C0402,C1525
1u 50V,C28,C0603,C15849
10u 25V,"C100,C101",C0805,C15850
220,"R14,R15,R20,R21,R54,R55,R56,R57",R1206,C17957
SS34F,"D17,D3",SMAF_L3.5-W2.6-LS4.7-RD-1,C18199199
10u,"C104,C33,C60,C99",C0603,C19702
AO3400A,"Q10,Q11,Q12,Q13",SOT-23_L2.9-W1.3-P1.90-LS2.4-BR,C20917
BAV99,"D10,D11",SOT-23_L2.9-W1.3-P1.90-LS2.4-BR,C2500
100,"R120,R121,R39",R0402,C25076
10,R145,R0402,C25077
680,R93,R0402,C25130
1,"R151,R157",R0805,C25271
100k,"R124,R125,R131,R135,R34,R36,R37,R50,R71,R77,R91",R0402,C25741
10k,"R158,R88",R0402,C25744
12k,"R32,R67",R0402,C25752
150k,R33,R0402,C25755
15k,"R136,R89",R0402,C25756
18k,R139,R0402,C25762
20k,"R153,R154,R30,R31,R65,R66",R0402,C25765
24k,R138,R0402,C25769
56k,"R160,R161",R0402,C25796
4.7k,R167,R0402,C25900
1M,"R134,R38",R0402,C26083
2.2n C0G,"C32,C67,C89,C90",C0603,C2991172
CJ431,U19,SOT-23-3_L2.9-W1.6-P1.90-LS2.8-BR,C3113
DOWN / NO / UP / YES,"SW1,SW3,SW4,SW5",SW-SMD_4P-L5.1-W5.1-P3.70-LS6.5-TL_H1.5,C318884
1.0u,L5,IND-SMD_L2.0-W1.6-1,C337892
BAT54C,D16,SOT-23-3_L2.9-W1.6-P1.90-LS2.8-BR,C37704
PESD15VL2BT,"D14,D7",SOT-23_L2.9-W1.3-P1.90-LS2.4-BR,C38838
1k,"R75,R78,R81,R84",R1206,C4410
22u 25V,C27,C0805,C45783
1u,"C30,C31,C65,C66",C0402,C52923
SRV05-4,"U11,U12,U5",SOT-23-6_L2.9-W1.6-P0.95-LS2.8-BL-1,C7420376
74AHCT04,U21,TSSOP-14_L5.0-W4.4-P0.65-LS6.4-BL,C8190
TPS61023DRLR,U18,SOT-563_L1.6-W1.2-P0.50-LS1.6-BR,C919459

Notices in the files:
hardware/mini2/make_board.py:
(hardware/pcb/lib/stitch.py, after m-card's stitch(), CC0-1.0)
hardware/pcb/make_board.py:
(lib/stitch.py: from optimist's SD board, after m-card's stitch(), CC0-1.0)
